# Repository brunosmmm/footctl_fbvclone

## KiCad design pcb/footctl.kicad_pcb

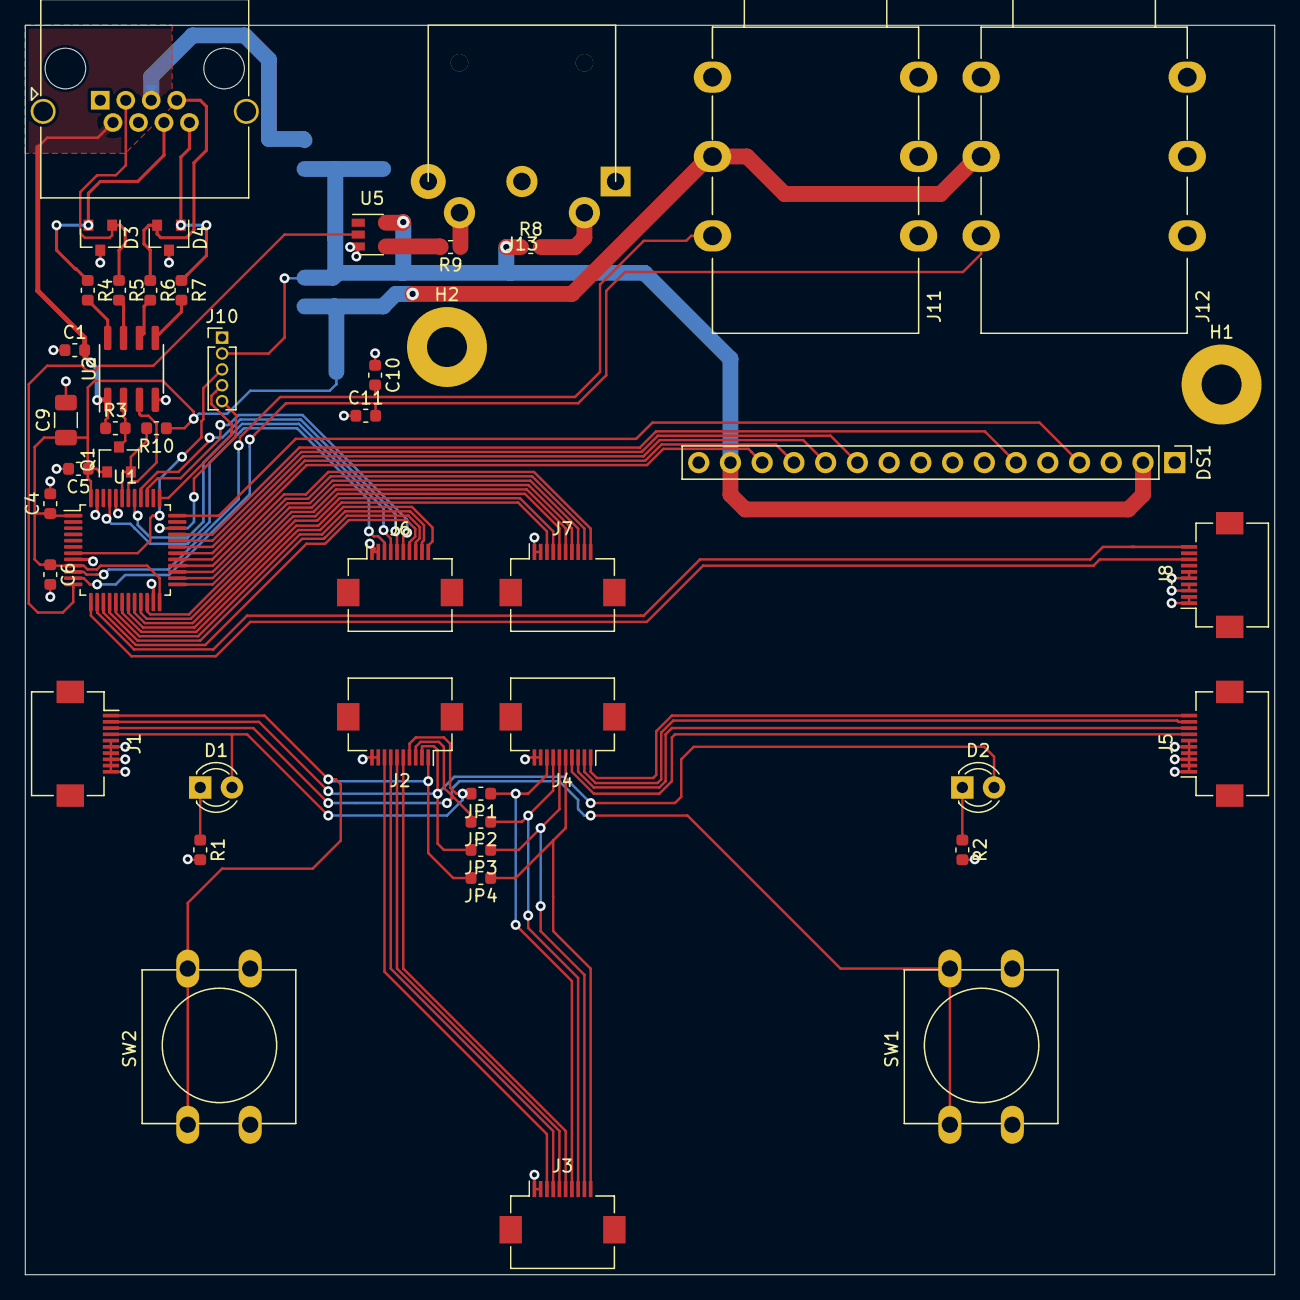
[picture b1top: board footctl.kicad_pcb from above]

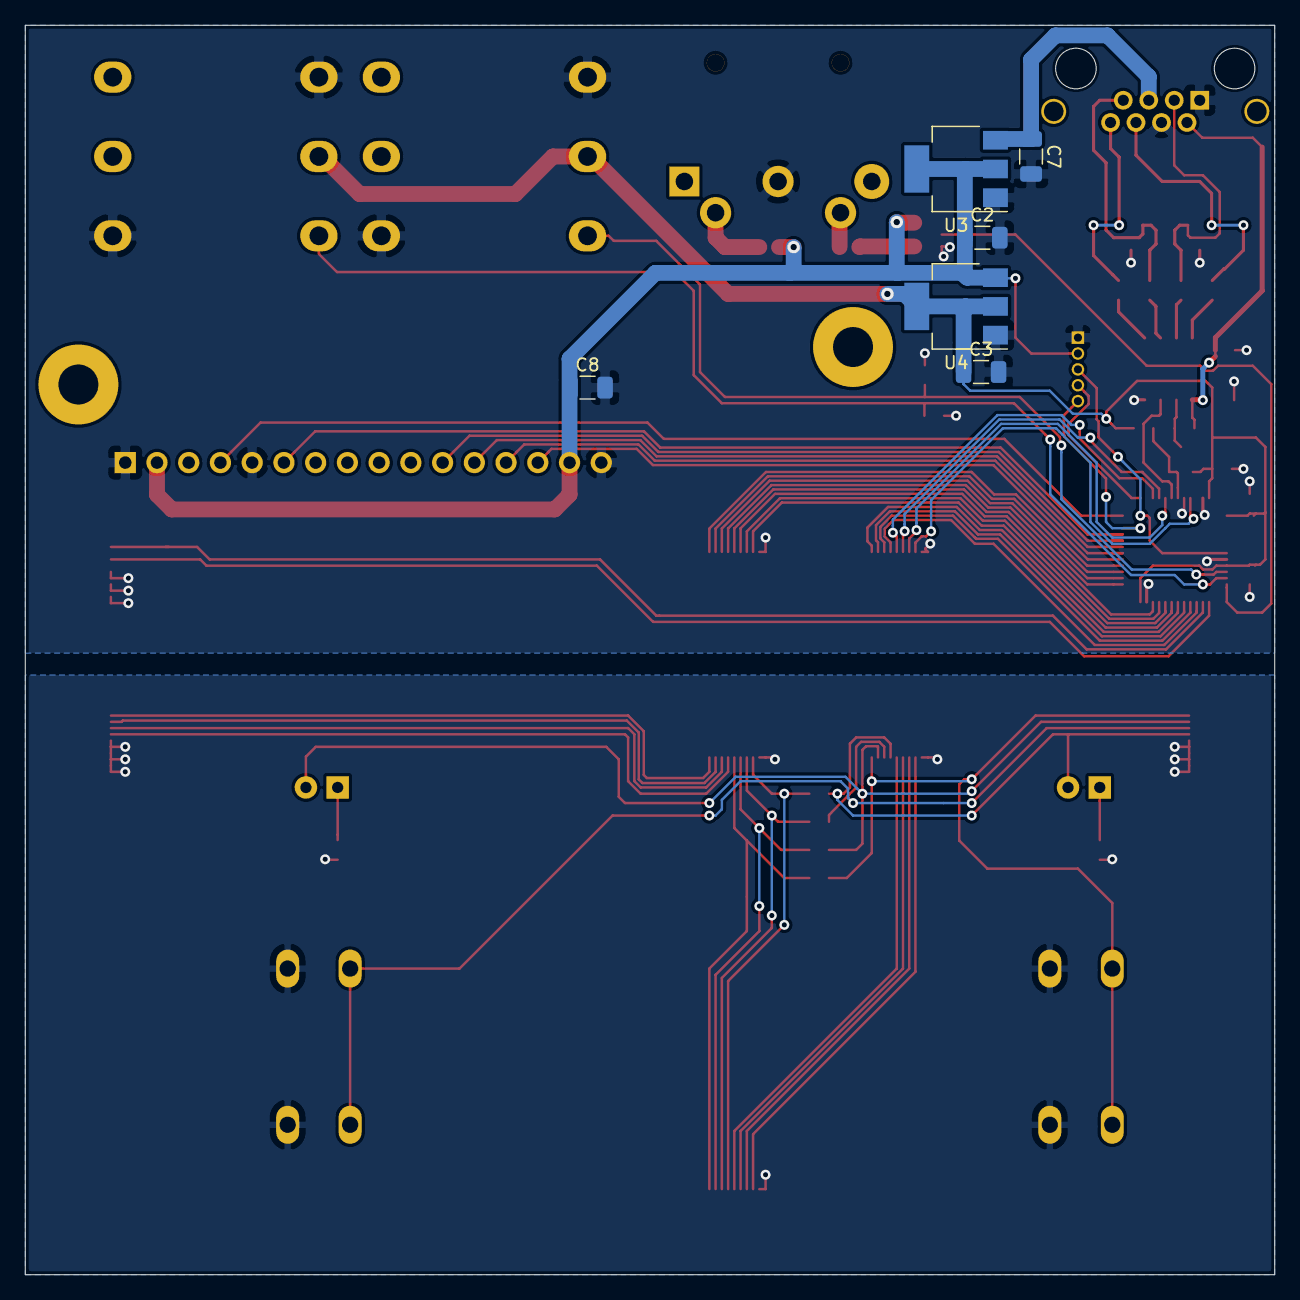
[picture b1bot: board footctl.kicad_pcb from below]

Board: 2 copper layers, 100.0 x 100.0 mm, 53 parts (6 on the bottom side), 65 nets.

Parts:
C1, C4, C5, C6: 0.1u; C_0603_1608Metric
C2, C3, C7, C8, C9: CP; C_1206_3216Metric
C10, C11: C; C_0603_1608Metric
D1, D2: LED; LED_D3.0mm
D3, D4: D_TVS_x2_AAC; SOT-23
DS1: WC1602A; PinHeader_1x16_P2.54mm_Vertical
H1, H2: MountingHole; MountingHole_3.2mm_M3_Pad
J1: W; Hirose_FH12-10S-0.5SH_1x10-1MP_P0.50mm_Horizontal
J2: NE; Hirose_FH12-10S-0.5SH_1x10-1MP_P0.50mm_Horizontal
J3, J6: SW; Hirose_FH12-10S-0.5SH_1x10-1MP_P0.50mm_Horizontal
J4: NW; Hirose_FH12-10S-0.5SH_1x10-1MP_P0.50mm_Horizontal
J5: E; Hirose_FH12-10S-0.5SH_1x10-1MP_P0.50mm_Horizontal
J7: SE; Hirose_FH12-10S-0.5SH_1x10-1MP_P0.50mm_Horizontal
J8: UPDOWN; Hirose_FH12-10S-0.5SH_1x10-1MP_P0.50mm_Horizontal
J9: RJ45; RJ45_Amphenol_RJHSE5380
J10: PROG; PinHeader_1x05_P1.27mm_Vertical
J11: EXP2; NYS126
J12: EXP1; NYS126
J13: Conn_01x05_Female; KCDX-5S-N
JP1, JP2, JP3, JP4: Jumper; R_0603_1608Metric
Q1: 2N7002; SOT-23
R1, R2: R; R_0603_1608Metric
R3: 10K; R_0603_1608Metric
R4, R5, R6, R7: 10; R_0603_1608Metric
R8, R9: 220; R_0603_1608Metric
R10: 10k; R_0603_1608Metric
SW1, SW2: SW_SPST; SW_PUSH-12mm
U1: STM32F030C8Tx; LQFP-48_7x7mm_P0.5mm
U2: THVD1451; SOIC-8_3.9x4.9mm_P1.27mm
U3: LD1117S50TR_SOT223; SOT-223-3_TabPin2
U4: LD1117S33TR_SOT223; SOT-223-3_TabPin2
U5: 74AUC1G17; SOT-23-5

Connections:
+3V3: C3.1, C4.1, C5.1, C6.1, C9.1, J11.R1, J12.R1, Q1.1, R10.1, U1.1, U1.9, U1.24, U1.48, U4.2
+5V: C2.1, C8.1, DS1.2, DS1.15, J10.2, R8.1, U3.2, U4.3, U5.5
/ELED1: J4.4, J5.7
/ELED2: J4.2, J5.9
/ESW1: J4.3, J5.8
/ESW2: J4.1, J5.10
/EXP1: C10.2, J11.T1, U1.10
/EXP2: C11.2, J12.T1, U1.11
/IOLED0: J7.9, U1.27
/IOLED1: J7.7, U1.25
/IOLED2: J7.5, U1.21
/IOLED3: J7.3, U1.19
/IOLED4: J6.9, U1.17
/IOLED5: J6.7, U1.15
/IOLED6: J6.5, U1.40
/IOLED7: J6.3, U1.45
/IOSW0: J7.10, U1.28
/IOSW1: J7.8, U1.26
/IOSW2: J7.6, U1.22
/IOSW3: J7.4, U1.20
/IOSW4: J6.10, U1.18
/IOSW5: J6.8, U1.16
/IOSW6: J6.6, U1.39
/IOSW7: J6.4, U1.41
/IOSW8: J8.10, U1.14
/LCDD4: DS1.11, U1.32
/LCDD5: DS1.12, U1.31
/LCDD6: DS1.13, U1.30
/LCDD7: DS1.14, U1.29
/LCDE: DS1.6, U1.33
/LCDRS: DS1.4, U1.36
/LED1: D1.2, J1.4, J2.4, JP1.2
/LED2: D2.2, J1.2, J2.2, JP3.2
/MIDI_TX: U1.12, U5.2
/NRST: J10.3, U1.7
/RX: Q1.2, R10.2, U1.43
/RX+: D3.2, J9.6, R4.1
/RX-: D3.1, J9.3, R5.1
/SLED1: J3.7, J4.8, JP1.1
/SLED2: J3.9, J4.6, JP3.1
/SLED3: J2.8, J3.3
/SLED4: J2.6, J3.5
/SSW1: J3.8, J4.7, JP2.1
/SSW2: J3.10, J4.5, JP4.1
/SSW3: J2.7, J3.4
/SSW4: J2.5, J3.6
/SW1: J1.3, J2.3, JP2.2, SW1.1
/SW2: J1.1, J2.1, JP4.2, SW2.1
/SWCLK: J10.4, U1.37
/SWDIO: J10.5, U1.34
/TX: U1.42, U2.3
/TX+: D4.1, J9.8, R7.1
/TX-: D4.2, J9.7, R6.1
GND: C1.1, C2.2, C3.2, C4.2, C5.2, C6.2, C7.2, C8.2, C9.2, C10.1, C11.1, D3.3, D4.3, DS1.1, DS1.5, DS1.16, J1.5, J1.6, J1.7, J1.8, J1.9, J1.10, J2.9, J2.10, J3.1, J3.2, J4.9, J4.10, J5.1, J5.2, J5.3, J5.4, J5.5, J5.6, J6.1, J6.2, J7.1, J7.2, J8.1, J8.2, J8.3, J8.4, J8.5, J8.6, J9.1, J9.4, J10.1, J11.S1, J11.TN1, J12.S1, J12.TN1, J13.2, R1.2, R2.2, SW1.2, SW2.2, U1.8, U1.23, U1.44, U1.47, U2.4, U3.1, U4.1, U5.3
unnamed: D1.1, R1.1
unnamed: D2.1, R2.1
unnamed: J13.4, R8.2
unnamed: J13.5, R9.1
unnamed: Q1.3, R3.2, U2.2
unnamed: R4.2, U2.8
unnamed: R5.2, U2.7
unnamed: R6.2, U2.6
unnamed: R7.2, U2.5
unnamed: R9.2, U5.4
VDD: C1.2, C7.1, J9.2, J9.5, R3.1, U2.1, U3.3

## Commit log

2019-10-26 rename, delete, add, etc
2019-10-26 update fiels
2019-10-27 implement debug tools to help figure out protocol
2019-10-28 implement initial FBV library
2019-10-28 stub
2019-10-28 implement and experiment more, not working w/ bod xt
2019-10-28 test
2019-10-28 test more, fix
2019-10-28 automatically make string null terminated
2019-10-28 ginore more
2019-10-29 make threaded, still does not work
2019-10-29 added some fixes, reverse engineer more a bit
2019-10-29 fix inspect script
2019-10-29 search entire command space in capture; other tweaks
2019-10-29 search properly
2019-10-29 implement searching properly
2019-10-29 fix usage of arguments
2019-10-29 fix formatting
2019-10-29 begin implementation of POD MIDI control
2019-10-29 tweak
2019-10-29 build all dependencies
2019-10-29 add root Makefile
2019-10-29 partially implement required logic
2019-10-29 implement some more stubs for I/O
2019-10-29 forgot main io
2019-10-30 implement stubs for time primitive
2019-10-30 implement simple debouncing algorithm
2019-10-30 implement program number decoding and activation by switches
2019-10-30 implement more functionality
2019-10-30 implement button holding detection and tuner mode switching
2019-10-30 only send tap on btn release due to hold behavior
2019-10-30 implement stubs for verification w/o hardware
2019-10-30 add PCB files
2019-10-30 add .gitignore
2019-10-30 update pcb
2019-10-30 update Makefile
2019-10-30 stub for expression pedal polling
2019-10-30 implement expression pedal state change
2019-10-30 rename time.c/h
2019-10-30 implement virtual tick for debugging
2019-10-30 fix packet size
2019-10-30 actually update timers
2019-10-30 virtual device implementation
2019-10-30 virtual device
2019-10-30 invert condition order
2019-10-30 disable endless pinging by default
2019-10-30 invert RX/TX order
2019-10-30 receive MIDI in virtual device
2019-10-30 implement more virtual functionality
2019-10-31 fix wrong midi message bytes
2019-10-31 implement a bit more, fix typo
2019-10-31 implement FX state change
2019-10-31 avoid unnecessary midi messages
2019-10-31 implement full program change state
2019-10-31 implement some control changes
2019-10-31 add some footprints
2019-11-01 updated pcb
2019-11-01 update for dual target development
2019-11-01 update schematic and pcb with correct rs485 driver wiring
2019-11-01 update more
2019-11-01 implement target specific code
2019-11-01 update implementation with GPIO pins
2019-11-01 do not connect LCD RW pin
2019-11-02 modify a bit for pre-pcb development
2019-11-02 initialize depending on usage
2019-11-02 start implementing specific components
2019-11-02 fix IO mess
2019-11-02 assign pins for development
2019-11-02 add accessible port definitions
2019-11-02 update code
2019-11-02 annoying API difference from F0 to F1 devices
2019-11-02 implement button state reading
2019-11-02 wire usarts
2019-11-02 implement tick
2019-11-02 icnrease tick variable size and implement blocking wait
2019-11-02 lcd stuff
2019-11-02 implement dumb lcd driver
2019-11-02 wire lcd functions
2019-11-02 use initial text
2019-11-02 fixed a couple of things, runs well
2019-11-02 add openocd cfg
2019-11-02 pull ups dont work
2019-11-02 mitigate problems but USART still does not work properly
2019-11-04 clock frequency was incorrect
2019-11-04 wait more
2019-11-04 works more or less
2019-11-04 invert button polarity, fix state manipulation
2019-11-04 fix controller values
2019-11-04 many fixes
2019-11-04 more sensible lcd driver
2019-11-04 make it slower
2019-11-04 fix midi channel number
2019-11-04 fix midi
2019-11-04 play with lcd a bit more, make it work
2019-12-11 mostly complete pcb, needs v-groove
2020-08-10 Fix some stuff
2020-08-10 Why is this needed
2020-08-11 Fix compilation for real target
